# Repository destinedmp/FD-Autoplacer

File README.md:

# FD-Autoplacer

**A GPU-accelerated, force-directed PCB component autoplacer for KiCad 6+ boards.**

It reads a `.kicad_pcb` file, optimizes component placement using differentiable gradient descent on PyTorch tensors, and writes the result back to a new `.kicad_pcb` file — ready to open directly in KiCad and hand off to an autorouter.

---

## How It Works

### The Core Idea

Placement is formulated as a **continuous optimization problem**: given $N$ components with positions $(x_i, y_i, \theta_i)$, find the configuration that minimizes a weighted sum of differentiable cost terms. Because every term is smooth, PyTorch's autograd computes exact analytical gradients and the AdamW optimizer descends toward the minimum in seconds.

This is a significant step up from classic force-directed placement: instead of applying simplified spring forces in discrete Euler steps and hoping for convergence, the full gradient of the entire objective is computed and used directly.

---

## Architecture

```
main.py              Entry point, KiCad parser, visualization
optim_engine.py      GPU/CPU differentiable placement engine (PyTorch)
kicad_exporter.py    S-expression writer — exports placed file back to KiCad
tests/               Sample .kicad_pcb boards
```

### `main.py` — Parser & Optimization Driver

Contains two core parts:

1. **KiCad 6+ S-expression parser** (`parse_sexp`, `import_kicad_pcb`)
   - Parses `footprint`, `pad`, `net`, `fp_text`, `gr_line`, `gr_arc`, `gr_rect` nodes
   - Extracts component reference, position, rotation, pad positions, and net names
   - Reconstructs the `Edge.Cuts` board boundary into a polygon using segment chaining
   - Negates the Y axis on read (KiCad uses Y-down; internally Y-up is used throughout)

2. **Visualization & Utilities** (`draw`, `optimize_swap_group`)
   - matplotlib rendering of board polygon, net ratsnest lines, component boxes, and pin locations
   - Hungarian algorithm pin-swap optimization (`scipy.optimize.linear_sum_assignment`) to re-assign equivalent symmetric pins to reduce total wirelength after spatial placement

### `optim_engine.py` — GPU Optimization Engine

#### `PlacementProblem`
Encodes all parsed data into PyTorch tensors on the selected device:
- `half_sizes` `(N, 2)` — component bounding half-extents
- `is_free` `(N,)` — mask for movable vs. fixed components
- `nets` — list of dicts, each containing index arrays and pin local offsets for one net
- `decoup` — heuristically detected (bypass cap → IC) pairs for grouping springs

#### `PlacerModel` (`nn.Module`)
Holds three learnable parameters:

| Parameter | Shape | Description |
|-----------|-------|-------------|
| `X` | `(N,)` | Component X centres |
| `Y` | `(N,)` | Component Y centres |
| `Theta` | `(N,)` | Component rotation (radians) |

**Loss terms:**

| Term | Formula | Purpose |
|------|---------|---------|
| **LSE Wirelength** | `γ·(logsumexp(x/γ) + logsumexp(-x/γ) + …)` | Smooth HPWL approximation — pulls same-net pins together. Power nets weighted 0.05× |
| **Overlap** | `Σ relu(sx−dx)·relu(sy−dy)` over all pairs | Pairwise AABB intersection area using rotation-aware extents |
| **Boundary** | `Σ relu(bmin−corner)² + relu(corner−bmax)²` | Quadratic penalty for exceeding board bounding box |
| **Orientation** | `Σ sin²(2θ)` | Periodic snap with minima at 0°, 90°, 180°, 270° |
| **Decoupling** | `Σ relu(dist − target)²` | Proximity springs between detected bypass caps and their IC |

#### Three-Phase Pipeline

```
Phase 1 — Global Placement (default 1500 iters)
   AdamW + CosineAnnealingLR
   Weight schedule: overlap 10→310, boundary 50→350, LSE gamma 10→1, orient 0→8
   Gradually enforces non-overlap while minimizing wirelength

Phase 2 — Legalization
   Hard-snap every θ to the nearest multiple of 90° (no gradient)

Phase 3 — Refinement (400 iters)
   θ frozen; very high overlap (500×) and boundary (500×) weights
   Resolves any residual collisions while continuing to minimize wirelength
```

After all three phases, `project_position` projects each component centroid into the actual board polygon (the GPU model only enforces the axis-aligned bounding box), and a final Hungarian pin-swap pass is run.

### `kicad_exporter.py` — Round-Trip Writer

- Parses the original `.kicad_pcb` into an S-expression AST
- Walks every `footprint` node, looks up the optimized position from the `Component` dict
- Updates the `(at X Y θ)` field in-place, converting back to KiCad's Y-down coordinate system and degrees
- Serializes the full AST back to a formatted string preserving all non-placement data (tracks, zones, copper fills, text, design rules, etc.)

---

## Installation

```bash
git clone https://github.com/destinedmp/FD-Autoplacer
cd FD-Autoplacer
python -m venv .venv
.venv\Scripts\activate        # Windows
# source .venv/bin/activate   # macOS/Linux
pip install -r requirements.txt
```

**Dependencies:** `numpy`, `scipy`, `matplotlib`, `torch`

For GPU acceleration, PyTorch will automatically use CUDA if a compatible GPU and drivers are present. CPU fallback is automatic.

---

## Usage

```bash
# Optimize a board (GPU if available, otherwise CPU)
python main.py path/to/board.kicad_pcb

# Force CPU even when CUDA is present
python main.py path/to/board.kicad_pcb --cpu

# Tune the optimizer
python main.py path/to/board.kicad_pcb --iters 2000 --lr 0.03

# Export placed positions back to a KiCad file
python main.py path/to/board.kicad_pcb --export path/to/board_placed.kicad_pcb

# Keep original positions (don't scramble before placing)
python main.py path/to/board.kicad_pcb --no-scramble
```

All runs save a `placement.png` side-by-side comparison of the initial and converged layouts.

### CLI Reference

| Flag | Default | Description |
|------|---------|-------------|
| `pcb` | `tests/simple.kicad_pcb` | Path to input `.kicad_pcb` file |
| `--cpu` | off | Force CPU even when CUDA is available |
| `--iters N` | 1500 | Global placement iterations |
| `--lr F` | 0.05 | AdamW learning rate |
| `--export PATH` | none | Write placed PCB to this file |
| `--no-scramble` | off | Don't randomize positions before placement |

---

## Results

On `tests/leds.kicad_pcb` (99 components, 51 nets, complex cross-shaped board outline):

| Metric | Initial | Converged |
|--------|---------|-----------|
| Wirelength (LSE HPWL) | 4,059 | 2,100 |
| Overlap area | 781 | ~0 |
| Boundary violations | 0 | ~0 |
| Runtime (CPU) | — | ~47 seconds |

---

## Constraints & Design Rules Supported

| Constraint | How it's handled |
|-----------|-----------------|
| Board outline (any polygon) | Parsed from `Edge.Cuts` layer (`gr_line`, `gr_arc`, `gr_rect`). Used for post-GPU polygon projection |
| Fixed components | `fixed=True` — gradients zeroed; positions never updated |
| Allowed orientations | Snapped during legalization and final pass |
| Component keep-in zone | Per-component `allowed_rect` or `allowed_polygon` |
| Pin swapping | Hungarian assignment on equivalent-pin swap groups after placement |

---

## Theory

Classic **force-directed placement** models components as charged particles that repel each other and nets as springs that attract connected pins. The system is simulated until it reaches mechanical equilibrium.

The optimizer in this project replaces the simulation with **direct gradient descent** on a differentiable objective. The key insight is the **Log-Sum-Exp (LSE) wirelength approximation**:

$$\text{HPWL}(e) \approx \gamma \left( \log \sum_{i \in e} e^{x_i/\gamma} + \log \sum_{i \in e} e^{-x_i/\gamma} + \log \sum_{i \in e} e^{y_i/\gamma} + \log \sum_{i \in e} e^{-y_i/\gamma} \right)$$

As $\gamma \to 0$ this converges exactly to $\max(x) - \min(x) + \max(y) - \min(y)$, the true half-perimeter wirelength. Using a finite $\gamma$ keeps the function smooth so gradients flow through it cleanly. The schedule anneals $\gamma$ from 10 down to 1 over the course of optimization.

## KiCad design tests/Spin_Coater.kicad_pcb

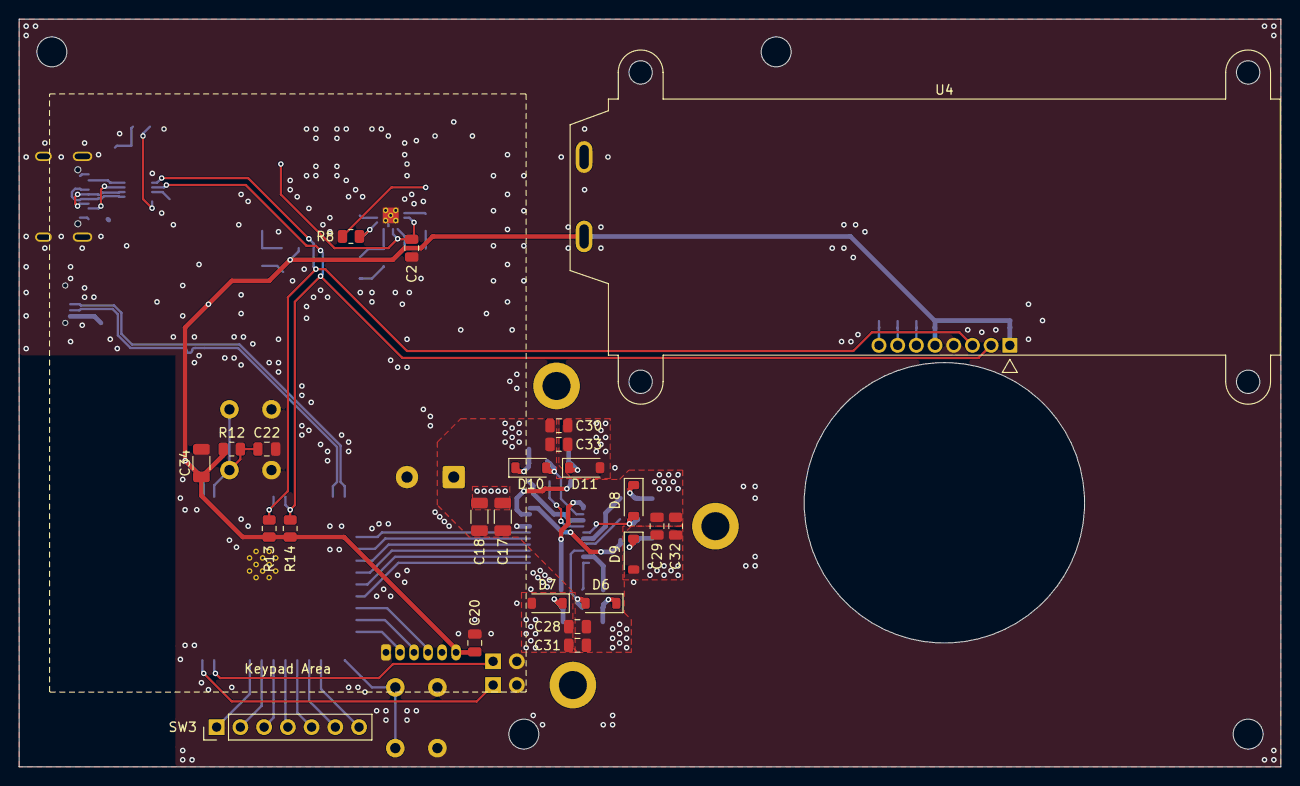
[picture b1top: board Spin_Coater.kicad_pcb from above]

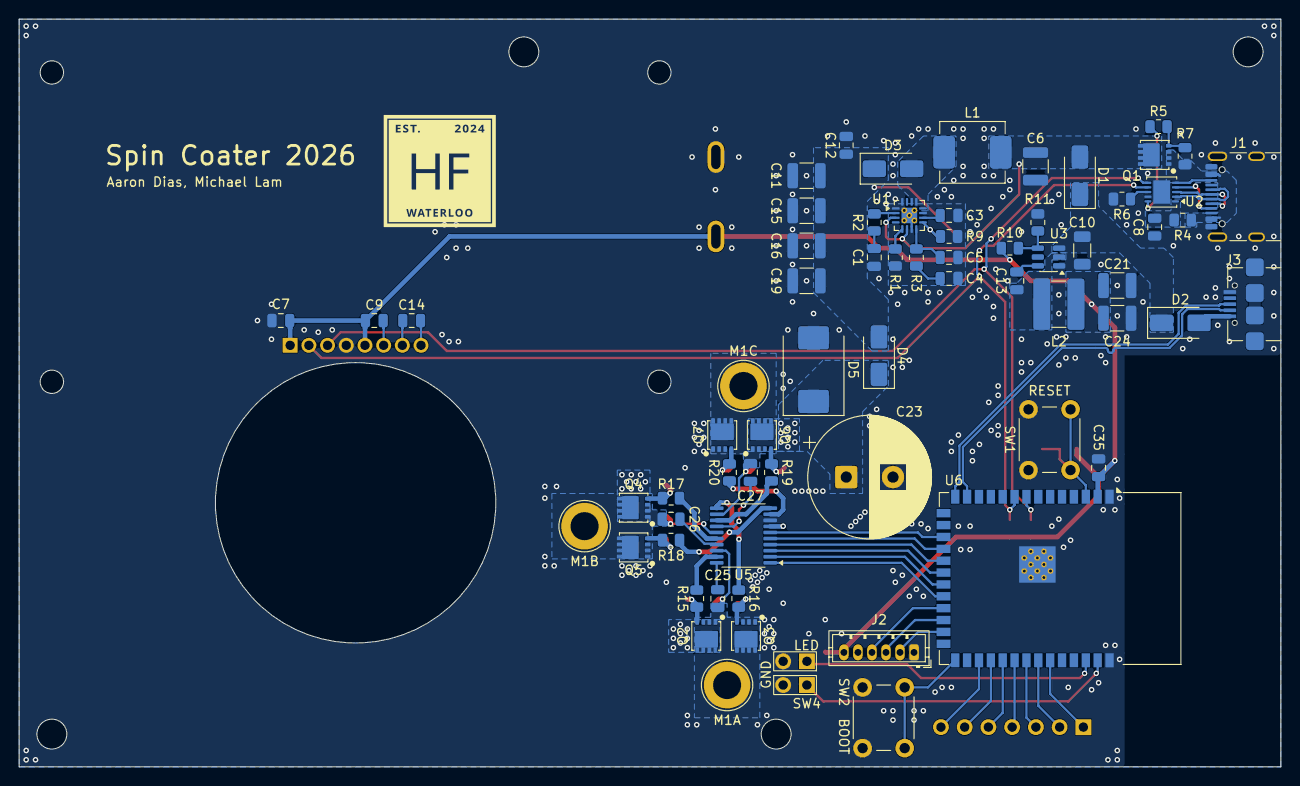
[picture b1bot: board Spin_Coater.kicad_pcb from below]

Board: 2 copper layers, 135.0 x 80.0 mm, 96 parts (68 on the bottom side), 73 nets.

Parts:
C1, C7, C8, C9, C14, C22, C25, C26, C27, C28, C29, C30, C31, C32, C33: 1uF; C_0805_2012Metric
C2, C12, C20, C35: 100nF; C_0805_2012Metric
C3, C4: 20nF; C_0805_2012Metric
C5: 220pF; C_0805_2012Metric
C6, C11, C15, C16, C19, C21, C24: 22uF; C_1210_3225Metric
C10, C17, C18, C34: 10uF; C_1206_3216Metric
C13: 330nF; C_0805_2012Metric
C23: 1mF; CP_Radial_D13.0mm_P5.00mm
D1, D2, D3, D4: B340AXF; D_SMA
D5: SMCJ15A; D_SMC
D6, D7, D8, D9, D10, D11: MMSZ5245B; D_SOD-123
H1, H2, H3, H4: MountingHole; MountingHole_3.2mm_M3
J1: USB_C_Receptacle_USB2.0_14P; UJ20-C-H-G-SMT-2A-P16-TR
J2: Motor Encoder In; JST_ZH_B6B-ZR_1x06_P1.50mm_Vertical
J3: USB_B_Micro; UJ2-MIBH-G-SMT-TR
L1: 5.6uH; HPAL1V0630
L2: 3.3uH; HPC5040NF
M1A, M1B, M1C: TestPoint; TestPoint_THTPad_D5.0mm_Drill3.0mm
NT1: NetTie_2; NetTie-2_SMD_Pad0.25mm
Q1: AONR21357; PPAK3x3
Q2, Q3, Q4, Q5, Q6, Q7: GSFN6982; PPAK3x3
R1, R7: 49.9k; R_0805_2012Metric
R2: 5.1; R_0805_2012Metric
R3: 2.8k; R_0805_2012Metric
R4: 10; R_0805_2012Metric
R5, R12, R13, R14: 5.1k; R_0805_2012Metric
R6: 10k; R_0805_2012Metric
R8: 18.7k; R_0805_2012Metric
R9: 1.65k; R_0805_2012Metric
R10: 66.5k; R_0805_2012Metric
R11: 20k; R_0805_2012Metric
R15, R16, R17, R18, R19, R20: 15; R_0805_2012Metric
SW1, SW2: SW_Push; SW_PUSH_6mm
SW3: Keypad; PinHeader_1x07_P2.54mm_Vertical
SW4: SW_Push_LED; PinSocket_2x02_P2.54mm_Vertical
U1: LM5157; WQFN-16-1EP_3x3mm_P0.5mm_EP1.68x1.68mm_ThermalVias
U2: HUSB238_xxxDD; WDFN-10-1EP_3x3mm_P0.5mm_EP1.8x2.5mm
U3: AP62200TWU; TSOT-23-6
U4: NHD-C0220BIZ; NHD-C0220BiZ
U5: DRV8300D; TSSOP-20_4.4x6.5mm_P0.65mm
U6: ESP32-S3-WROOM-1

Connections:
+3.3V: C7.1, C9.1, C20.2, C21.1, C24.1, C34.1, C35.1, J2.6, L2.2, R10.1, R12.1, R13.1, R14.1, U4.1 (~RST), U4.5 (VDD), U4.9 (A), U6.2 (3V3)
+12V: C17.1, C18.1, C23.1, C28.1, C29.1, C30.1, C31.1, C32.1, C33.1, D4.1 (K), D5.1 (A1), Q2.5 (D), Q4.5 (D), Q6.5 (D), U5.7 (GVDD)
/A: J2.2, U6.25 (IO48)
/B: J2.4, U6.23 (IO21)
/C: J2.3, U6.24 (IO47)
/INHA: U5.1 (INHA), U6.22 (IO14)
/INHB: U5.2 (INHB), U6.21 (IO13)
/INHC: U5.3 (INHC), U6.20 (IO12)
/INLA: U5.4 (INLA), U6.19 (IO11)
/INLB: U5.5 (INLB), U6.18 (IO10)
/INLC: U5.6 (INLC), U6.17 (IO9)
/J1-D+: J1.A6 (D+), J1.B6 (D+), U2.2 (D+)
/J1-D-: J1.A7 (D-), J1.B7 (D-), U2.3 (D-)
/J3-D+: J3.3 (D+), U6.14 (USB_D+)
/J3-D-: J3.2 (D-), U6.13 (USB_D-)
/LED: SW4.4 (A), U6.38 (IO2)
/SCL: R14.2, U2.7 (SCL), U4.2 (SCL), U6.9 (IO16)
/SDA: R13.2, U2.6 (SDA), U4.3 (SDA), U6.8 (IO15)
/SW: SW4.2, U6.39 (IO1)
GND: C1.1, C2.1, C6.2, C7.2, C8.2, C10.2, C11.2, C12.2, C15.1, C16.2, C17.2, C18.2, C19.2, C20.1, C21.2, C22.1, C23.2, C24.2, C28.2, C29.2, C30.2, C31.2, C32.2, C33.2, C34.2, C35.2, D5.2 (A2), D7.2 (A), D9.2 (A), D11.2 (A), J1.A1 (GND), J1.A12 (GND), J1.B1 (GND), J1.B12 (GND), J1.SH (SHIELD), J2.1, J3.5 (GND), J3.SH (Shield), NT1.1, Q3.1 (S), Q3.2 (S), Q3.3 (S), Q5.1 (S), Q5.2 (S), Q5.3 (S), Q7.1 (S), Q7.2 (S), Q7.3 (S), R6.2, R11.2, SW1.1, SW2.1, SW4.1, SW4.3 (K), U1.1 (PGND), U1.16 (PGND), U1.17 (PGND), U2.9 (ISET), U2.11 (GND), U3.1 (GND), U4.4 (VSS), U4.10 (K), U5.8 (GND), U6.1 (GND), U6.40 (GND), U6.41 (GND)
GNDA: C3.1, C4.2, C5.2, NT1.2, R1.1, R9.2, U1.7 (AGND), U1.11 (MODE)
unnamed: C1.2, R2.1
unnamed: C4.1, R3.2
unnamed: C10.1, D1.1 (K), D2.1 (K), U3.3 (IN)
unnamed: D3.2 (A), L1.2, U1.12 (SW), U1.13 (SW), U1.14 (SW)
unnamed: C11.1, C12.1, C15.2, C16.1, C19.1, D3.1 (K), D4.2 (A), R8.1
unnamed: C25.2, D6.2 (A), M1A.1 (1_1), Q2.1 (S), Q2.2 (S), Q2.3 (S), Q3.5 (D), U5.18 (SHA)
unnamed: D6.1 (K), Q2.4 (G), R15.2
unnamed: D7.1 (K), Q3.4 (G), R16.2
unnamed: C26.2, D8.2 (A), M1B.1 (1_1), Q4.1 (S), Q4.2 (S), Q4.3 (S), Q5.5 (D), U5.15 (SHB)
unnamed: D8.1 (K), Q4.4 (G), R17.2
unnamed: D9.1 (K), Q5.4 (G), R18.2
unnamed: C27.2, D10.2 (A), M1C.1 (1_1), Q6.1 (S), Q6.2 (S), Q6.3 (S), Q7.5 (D), U5.12 (SHC)
unnamed: D10.1 (K), Q6.4 (G), R19.2
unnamed: D11.1 (K), Q7.4 (G), R20.2
unnamed: J1.A5 (CC1), U2.4 (CC1)
unnamed: J1.B5 (CC2), U2.5 (CC2)
unnamed: J1.A4 (VBUS), J1.A9 (VBUS), J1.B4 (VBUS), J1.B9 (VBUS), Q1.1 (S), Q1.2 (S), Q1.3 (S), R4.1, R7.1
unnamed: Q1.4 (G), R5.2, R7.2
unnamed: SW3.1, U6.35 (IO42)
unnamed: SW3.2, U6.34 (IO41)
unnamed: SW3.3, U6.33 (IO40)
unnamed: SW3.4, U6.32 (IO39)
unnamed: SW3.5, U6.31 (IO38)
unnamed: SW3.6, U6.30 (IO37)
unnamed: SW3.7, U6.29 (IO36)
unnamed: C5.1, R3.1, U1.8 (COMP)
unnamed: R8.2, R9.1, U1.9 (FB)
unnamed: R1.2, U1.5 (RT)
unnamed: C3.2, U1.10 (SS)
unnamed: R2.2, U1.2 (VCC)
unnamed: R5.1, U2.10 (GATE)
unnamed: C8.1, R4.2, U2.1 (VIN)
unnamed: R6.1, U2.8 (VSET)
unnamed: C13.2, U3.6 (BST)
unnamed: R10.2, R11.1, U3.4 (FB)
unnamed: C13.1, L2.1, U3.2 (SW)
unnamed: C14.1, U4.7 (C1+)
unnamed: C14.2, U4.8 (C1-)
unnamed: C9.2, U4.6 (VOUT)
unnamed: C25.1, U5.20 (BSTA)
unnamed: C26.1, U5.17 (BSTB)
unnamed: C27.1, U5.14 (BSTC)
unnamed: R15.1, U5.19 (GHA)
unnamed: R17.1, U5.16 (GHB)
unnamed: R19.1, U5.13 (GHC)
unnamed: R16.1, U5.11 (GLA)
unnamed: R18.1, U5.10 (GLB)
unnamed: R20.1, U5.9 (GLC)
unnamed: C22.2, R12.2, SW1.2, U6.3 (EN)
unnamed: SW2.2, U6.27 (IO0)
VBUS: C2.2, C6.1, D1.2 (A), L1.1, Q1.5 (D), U1.3 (BIAS), U1.6 (EN)
VBUS2: D2.2 (A), J3.1 (VBUS)

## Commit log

2026-06-04 Integrate GPU-accelerated PyTorch placement engine, add new tests, and update README
2026-06-04 Improve AABB optimizer with coordinate jittering, softplus boundaries, and tuned scheduling
2026-06-05 Implement 2-layer PCB dynamic placement and layer-flipping exporter
2026-06-05 Refactor: split main.py into parser.py, legacy_fd.py, and lean main.py
2026-06-05 Add iterative hard projection and auto-detect pin-swap groups for all 2-pin passives
2026-06-05 Add simple 2-layer test circuit generator (generate_demo.py)
2026-06-05 Fix footprint layer parenthesis syntax in generate_demo.py
2026-06-05 Remove legacy animation GIF from README and repository
2026-06-05 Add legends, locked patterns, and metrics to placement visualization
